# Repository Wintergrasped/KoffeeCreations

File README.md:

# KoffeeCreations

Here you will find all the Open Source files for the KoffeeCreations.cc products P.S Every part of this github and our website is under active development.

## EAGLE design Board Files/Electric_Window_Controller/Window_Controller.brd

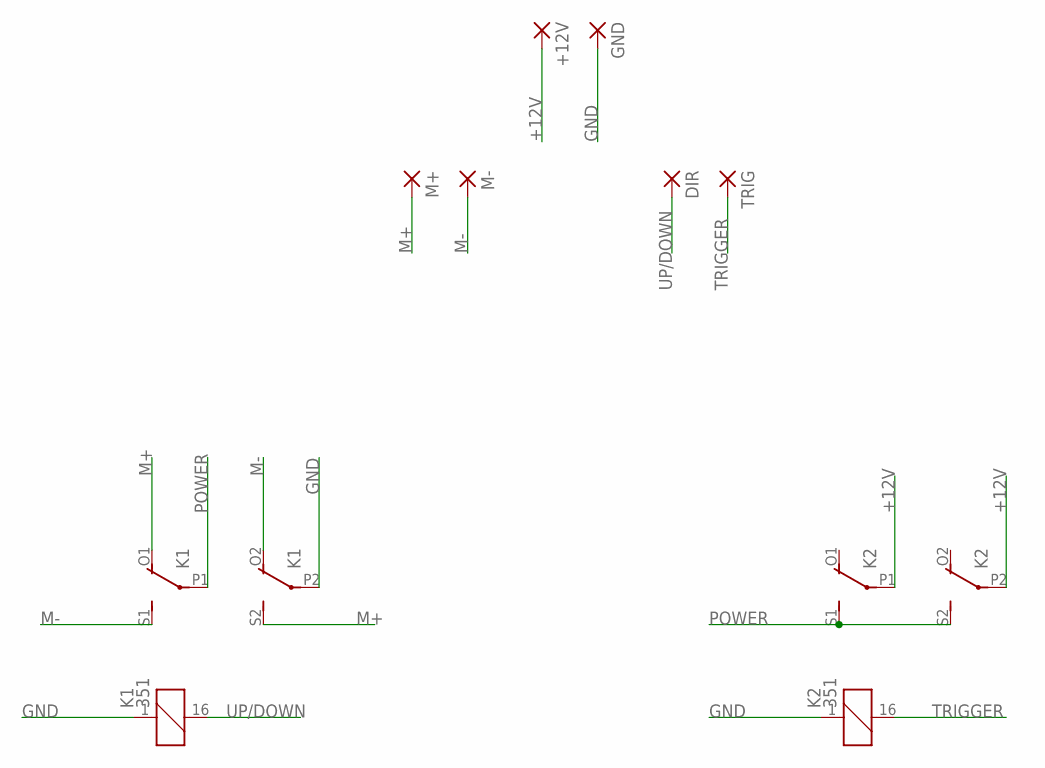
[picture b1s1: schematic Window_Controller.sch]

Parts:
+12V: 3,81/1,4
DIR: 3,81/1,4
GND: 3,81/1,4
K1, K2: 351
M+: 3,81/1,4
M-: 3,81/1,4
TRIG: 3,81/1,4

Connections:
+12V: +12V.1, K2.P1, K2.P2
GND: GND.1, K1.1, K1.P2, K2.1
M+: K1.O1 (O), K1.S2 (S), M+.1
M-: K1.O2 (O), K1.S1 (S), M-.1
POWER: K1.P1, K2.S1 (S), K2.S2 (S)
TRIGGER: K2.16 (2), TRIG.1
UP/DOWN: DIR.1, K1.16 (2)

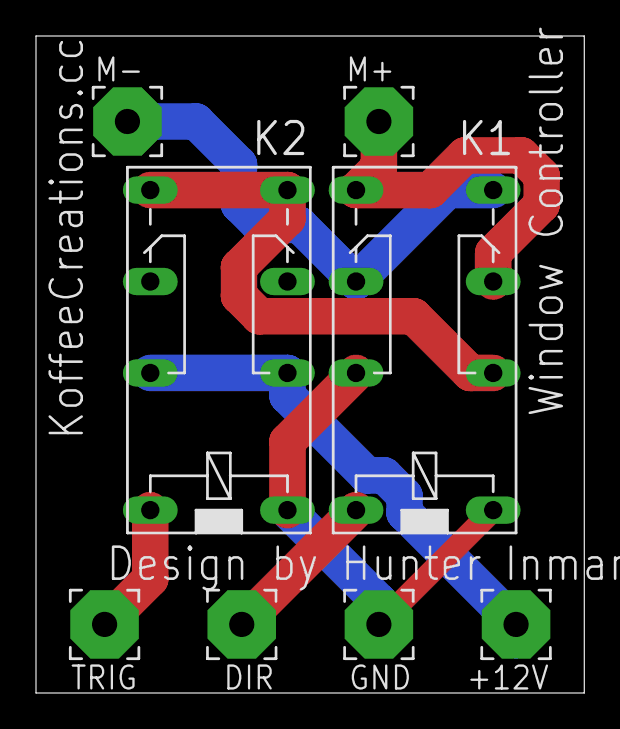
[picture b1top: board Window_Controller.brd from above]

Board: 2 copper layers, 30.5 x 36.5 mm, 8 parts (0 on the bottom side), 7 nets.

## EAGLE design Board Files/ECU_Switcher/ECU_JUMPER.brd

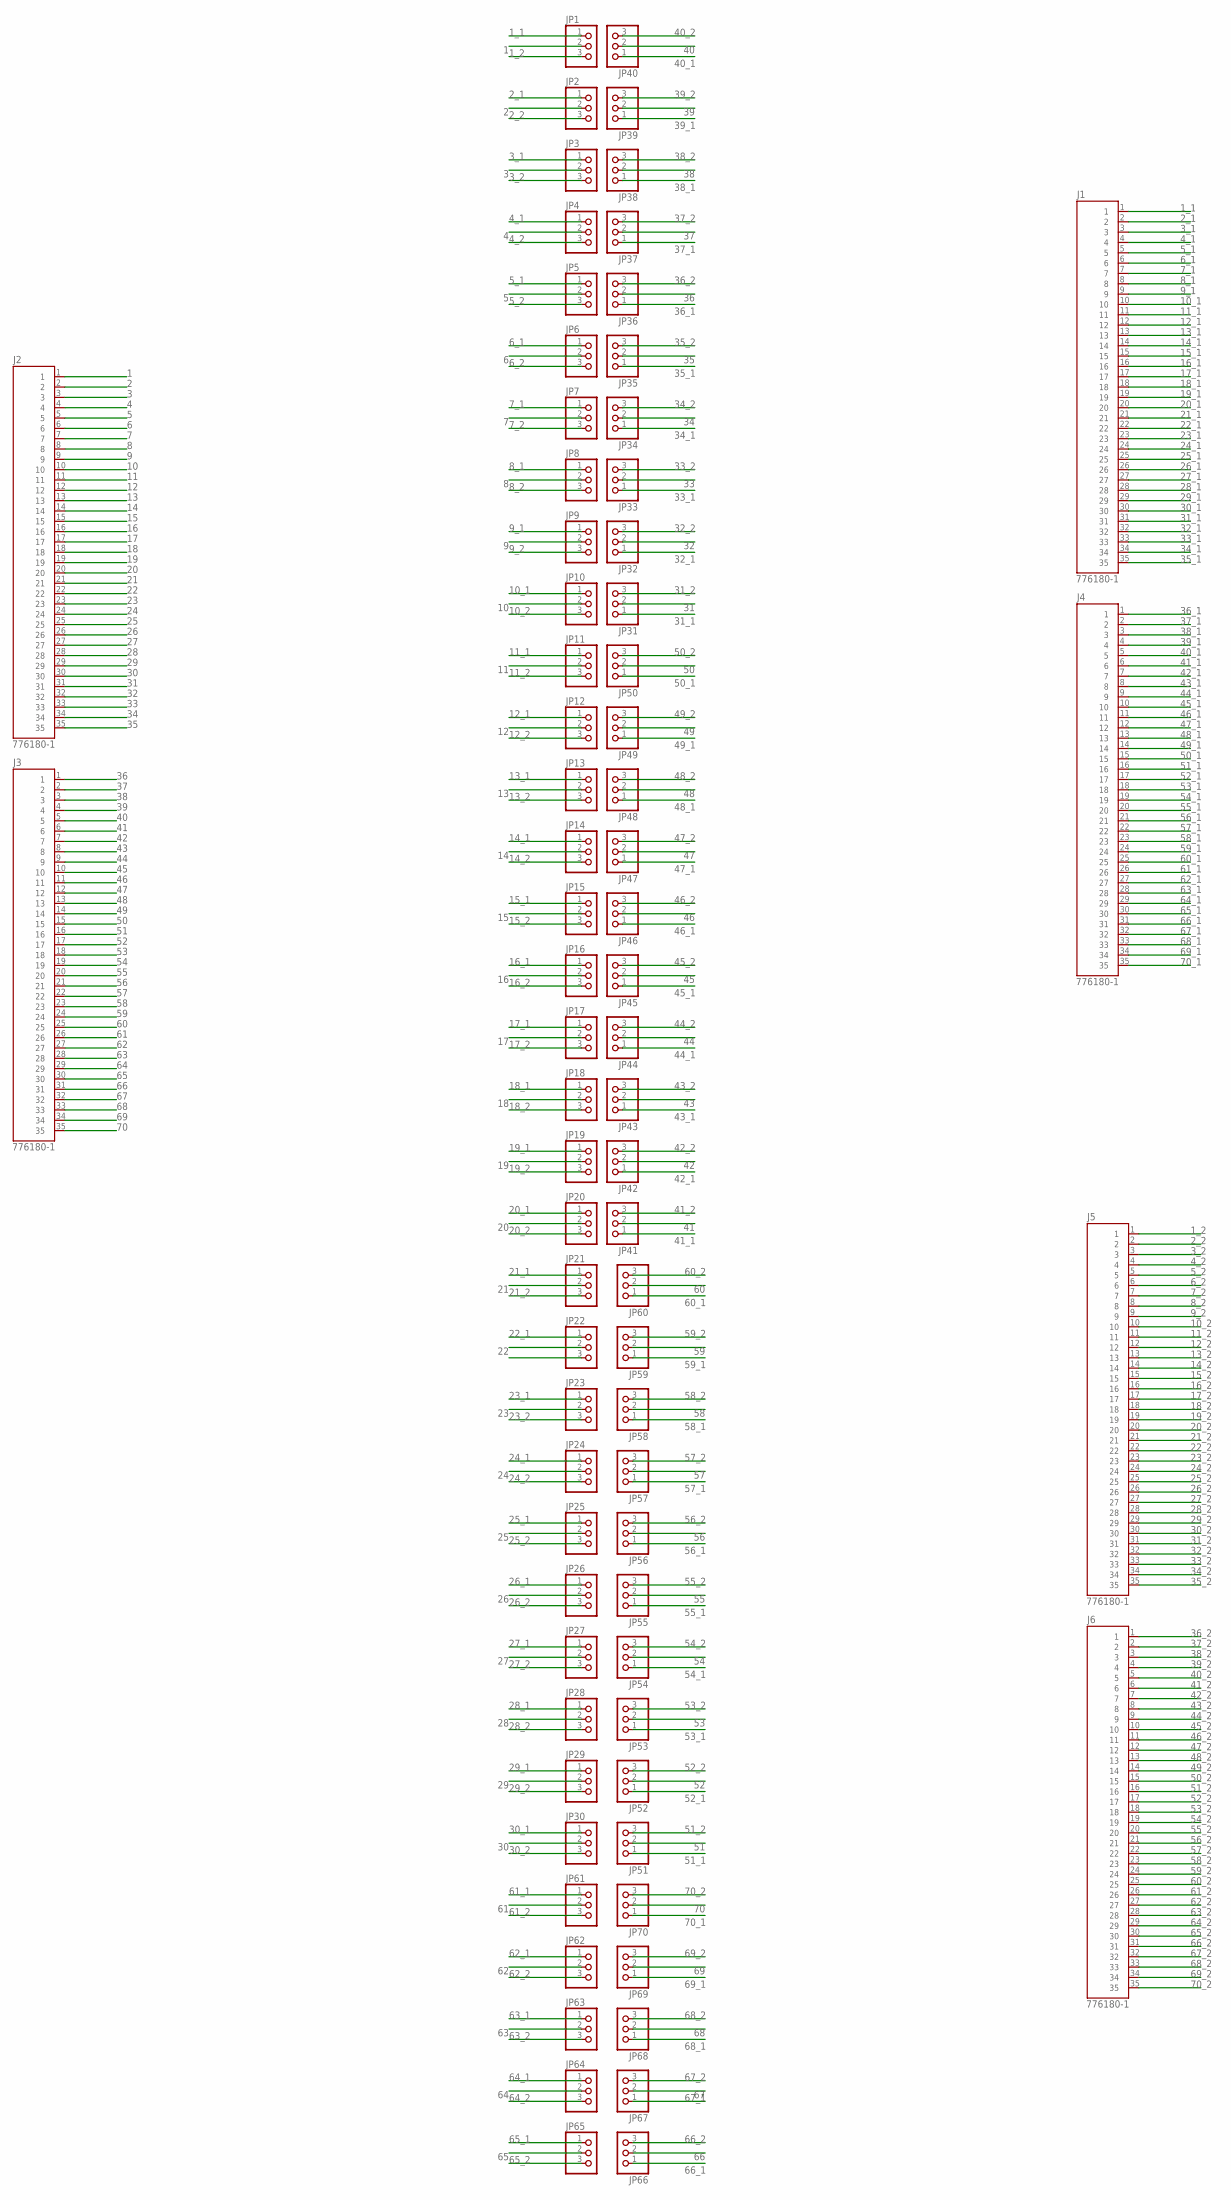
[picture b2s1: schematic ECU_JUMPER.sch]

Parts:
J1, J2, J3, J4, J5, J6: 776180-1; TE_776180-1
JP1, JP2, JP3, JP4, JP5, JP6, JP7, JP8, JP9, JP10, JP11, JP12, JP13, JP14, JP15, JP16, JP17, JP18, JP19, JP20, JP21, JP22, JP23, JP24, JP25, JP26, JP27, JP28, JP29, JP30, JP31, JP32, JP33, JP34, JP35, JP36, JP37, JP38, JP39, JP40, JP41, JP42, JP43, JP44, JP45, JP46, JP47, JP48, JP49, JP50, JP51, JP52, JP53, JP54, JP55, JP56, JP57, JP58, JP59, JP60, JP61, JP62, JP63, JP64, JP65, JP66, JP67, JP68, JP69, JP70: PINHD-1X3; 1X03

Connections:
1: J2.1, JP1.2
1_1: J1.1, JP1.1
1_2: J5.1, JP1.3
2: J2.2, JP2.2
2_1: J1.2, JP2.1
2_2: J5.2, JP2.3
3: J2.3, JP3.2
3_1: J1.3, JP3.1
3_2: J5.3, JP3.3
4: J2.4, JP4.2
4_1: J1.4, JP4.1
4_2: J5.4, JP4.3
5: J2.5, JP5.2
5_1: J1.5, JP5.1
5_2: J5.5, JP5.3
6: J2.6, JP6.2
6_1: J1.6, JP6.1
6_2: J5.6, JP6.3
7: J2.7, JP7.2
7_1: J1.7, JP7.1
7_2: J5.7, JP7.3
8: J2.8, JP8.2
8_1: J1.8, JP8.1
8_2: J5.8, JP8.3
9: J2.9, JP9.2
9_1: J1.9, JP9.1
9_2: J5.9, JP9.3
10: J2.10, JP10.2
10_1: J1.10, JP10.1
10_2: J5.10, JP10.3
11: J2.11, JP11.2
11_1: J1.11, JP11.1
11_2: J5.11, JP11.3
12: J2.12, JP12.2
12_1: J1.12, JP12.1
12_2: J5.12, JP12.3
13: J2.13, JP13.2
13_1: J1.13, JP13.1
13_2: J5.13, JP13.3
14: J2.14, JP14.2
14_1: J1.14, JP14.1
14_2: J5.14, JP14.3
15: J2.15, JP15.2
15_1: J1.15, JP15.1
15_2: J5.15, JP15.3
16: J2.16, JP16.2
16_1: J1.16, JP16.1
16_2: J5.16, JP16.3
17: J2.17, JP17.2
17_1: J1.17, JP17.1
17_2: J5.17, JP17.3
18: J2.18, JP18.2
18_1: J1.18, JP18.1
18_2: J5.18, JP18.3
19: J2.19, JP19.2
19_1: J1.19, JP19.1
19_2: J5.19, JP19.3
20: J2.20, JP20.2
20_1: J1.20, JP20.1
20_2: J5.20, JP20.3
21: J2.21, JP21.2
21_1: J1.21, JP21.1
21_2: J5.21, JP21.3
22: J2.22, JP22.2
22_1: J1.22, JP22.1
22_2: J5.22
23: J2.23, JP23.2
23_1: J1.23, JP23.1
23_2: J5.23, JP23.3
24: J2.24, JP24.2
24_1: J1.24, JP24.1
24_2: J5.24, JP24.3
25: J2.25, JP25.2
25_1: J1.25, JP25.1
25_2: J5.25, JP25.3
26: J2.26, JP26.2
26_1: J1.26, JP26.1
26_2: J5.26, JP26.3
27: J2.27, JP27.2
27_1: J1.27, JP27.1
27_2: J5.27, JP27.3
28: J2.28, JP28.2
28_1: J1.28, JP28.1
28_2: J5.28, JP28.3
29: J2.29, JP29.2
29_1: J1.29, JP29.1
29_2: J5.29, JP29.3
30: J2.30, JP30.2
30_1: J1.30, JP30.1
30_2: J5.30, JP30.3
31: J2.31, JP31.2
31_1: J1.31, JP31.1
31_2: J5.31, JP31.3
32: J2.32, JP32.2
32_1: J1.32, JP32.1
32_2: J5.32, JP32.3
33: J2.33, JP33.2
33_1: J1.33, JP33.1
33_2: J5.33, JP33.3
34: J2.34, JP34.2
34_1: J1.34, JP34.1
34_2: J5.34, JP34.3
35: J2.35, JP35.2
35_1: J1.35, JP35.1
35_2: J5.35, JP35.3
36: J3.1, JP36.2
36_1: J4.1, JP36.1
36_2: J6.1, JP36.3
37: J3.2, JP37.2
37_1: J4.2, JP37.1
37_2: J6.2, JP37.3
38: J3.3, JP38.2
38_1: J4.3, JP38.1
38_2: J6.3, JP38.3
39: J3.4, JP39.2
39_1: J4.4, JP39.1
39_2: J6.4, JP39.3
40: J3.5, JP40.2
40_1: J4.5, JP40.1
40_2: J6.5, JP40.3
41: J3.6, JP41.2
41_1: J4.6, JP41.1
41_2: J6.6, JP41.3
42: J3.7, JP42.2
42_1: J4.7, JP42.1
42_2: J6.7, JP42.3
43: J3.8, JP43.2
43_1: J4.8, JP43.1
43_2: J6.8, JP43.3
44: J3.9, JP44.2
44_1: J4.9, JP44.1
44_2: J6.9, JP44.3
45: J3.10, JP45.2
45_1: J4.10, JP45.1
45_2: J6.10, JP45.3
46: J3.11, JP46.2
46_1: J4.11, JP46.1
46_2: J6.11, JP46.3
47: J3.12, JP47.2
47_1: J4.12, JP47.1
47_2: J6.12, JP47.3
48: J3.13, JP48.2
48_1: J4.13, JP48.1
48_2: J6.13, JP48.3
49: J3.14, JP49.2
49_1: J4.14, JP49.1
49_2: J6.14, JP49.3
50: J3.15, JP50.2
50_1: J4.15, JP50.1
50_2: J6.15, JP50.3
51: J3.16, JP51.2
51_1: J4.16, JP51.1
51_2: J6.16, JP51.3
52: J3.17, JP52.2
52_1: J4.17, JP52.1
52_2: J6.17, JP52.3
53: J3.18, JP53.2
53_1: J4.18, JP53.1
53_2: J6.18, JP53.3
54: J3.19, JP54.2
54_1: J4.19, JP54.1
54_2: J6.19, JP54.3
55: J3.20, JP55.2
55_1: J4.20, JP55.1
55_2: J6.20, JP55.3
56: J3.21, JP56.2
56_1: J4.21, JP56.1
56_2: J6.21, JP56.3
57: J3.22, JP57.2
57_1: J4.22, JP57.1
57_2: J6.22, JP57.3
58: J3.23, JP58.2
58_1: J4.23, JP58.1
58_2: J6.23, JP58.3
59: J3.24, JP59.2
59_1: J4.24, JP59.1
59_2: J6.24, JP59.3
60: J3.25, JP60.2
60_1: J4.25, JP60.1
60_2: J6.25, JP60.3
61: J3.26, JP61.2
61_1: J4.26, JP61.1
61_2: J6.26, JP61.3
62: J3.27, JP62.2
62_1: J4.27, JP62.1
62_2: J6.27, JP62.3
63: J3.28, JP63.2
63_1: J4.28, JP63.1
63_2: J6.28, JP63.3
64: J3.29, JP64.2
64_1: J4.29, JP64.1
64_2: J6.29, JP64.3
65: J3.30, JP65.2
65_1: J4.30, JP65.1
65_2: J6.30, JP65.3
66: J3.31, JP66.2
66_1: J4.31, JP66.1
66_2: J6.31, JP66.3
67: J3.32, JP67.2
67_1: J4.32, JP67.1
67_2: J6.32, JP67.3
68: J3.33, JP68.2
68_1: J4.33, JP68.1
68_2: J6.33, JP68.3
69: J3.34, JP69.2
69_1: J4.34, JP69.1
69_2: J6.34, JP69.3
70: J3.35, JP70.2
70_1: J4.35, JP70.1
70_2: J6.35, JP70.3

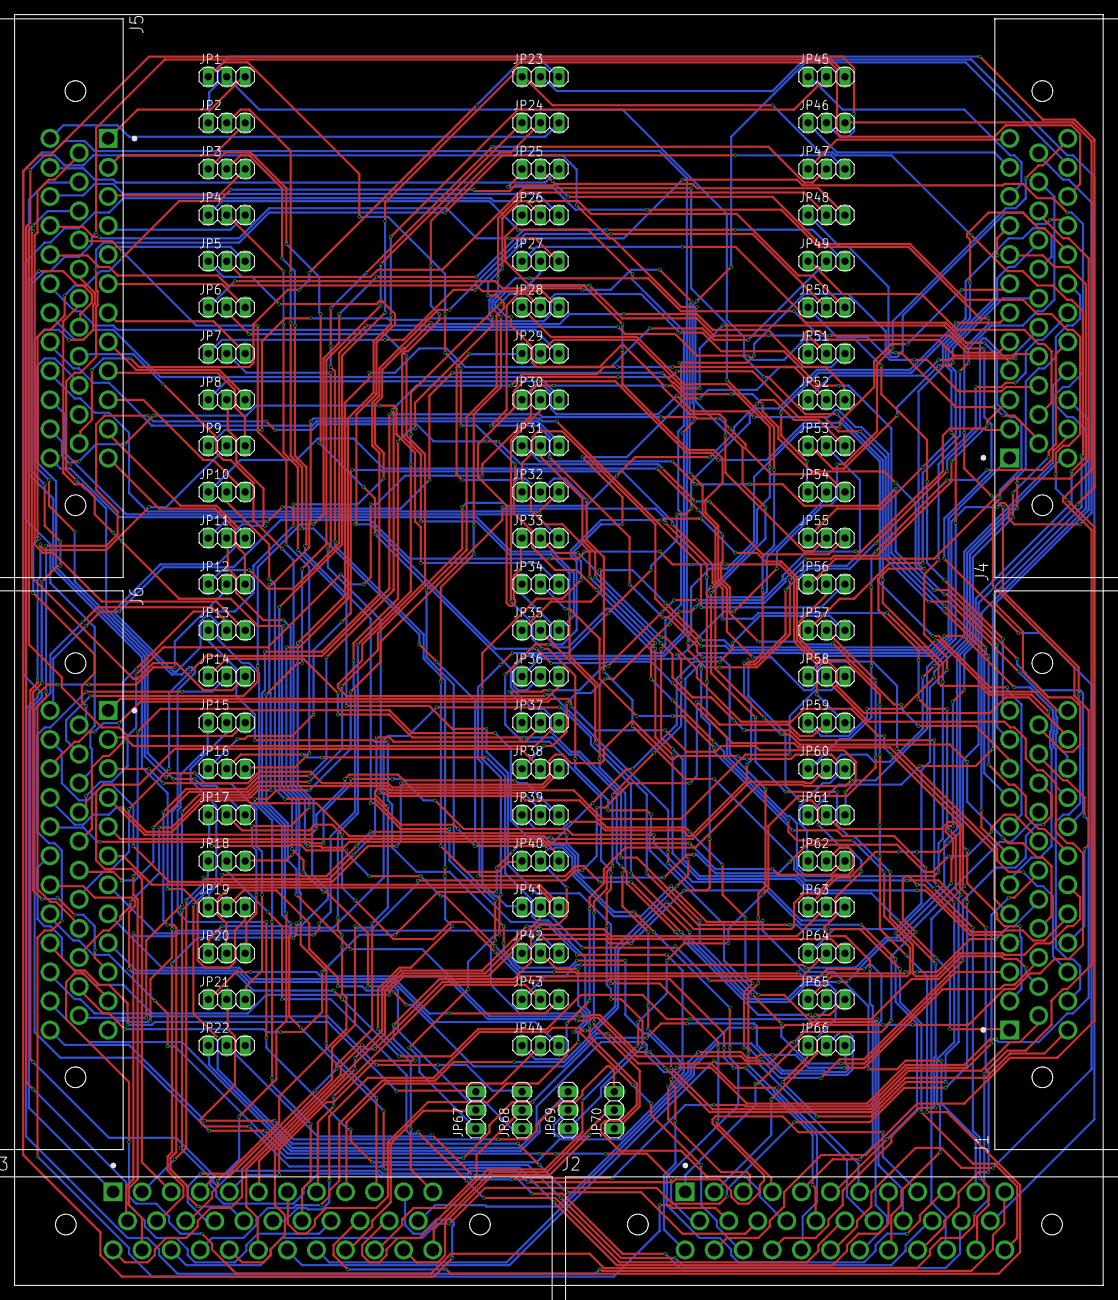
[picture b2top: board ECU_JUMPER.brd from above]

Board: 2 copper layers, 149.8 x 174.9 mm, 76 parts (0 on the bottom side), 209 nets.

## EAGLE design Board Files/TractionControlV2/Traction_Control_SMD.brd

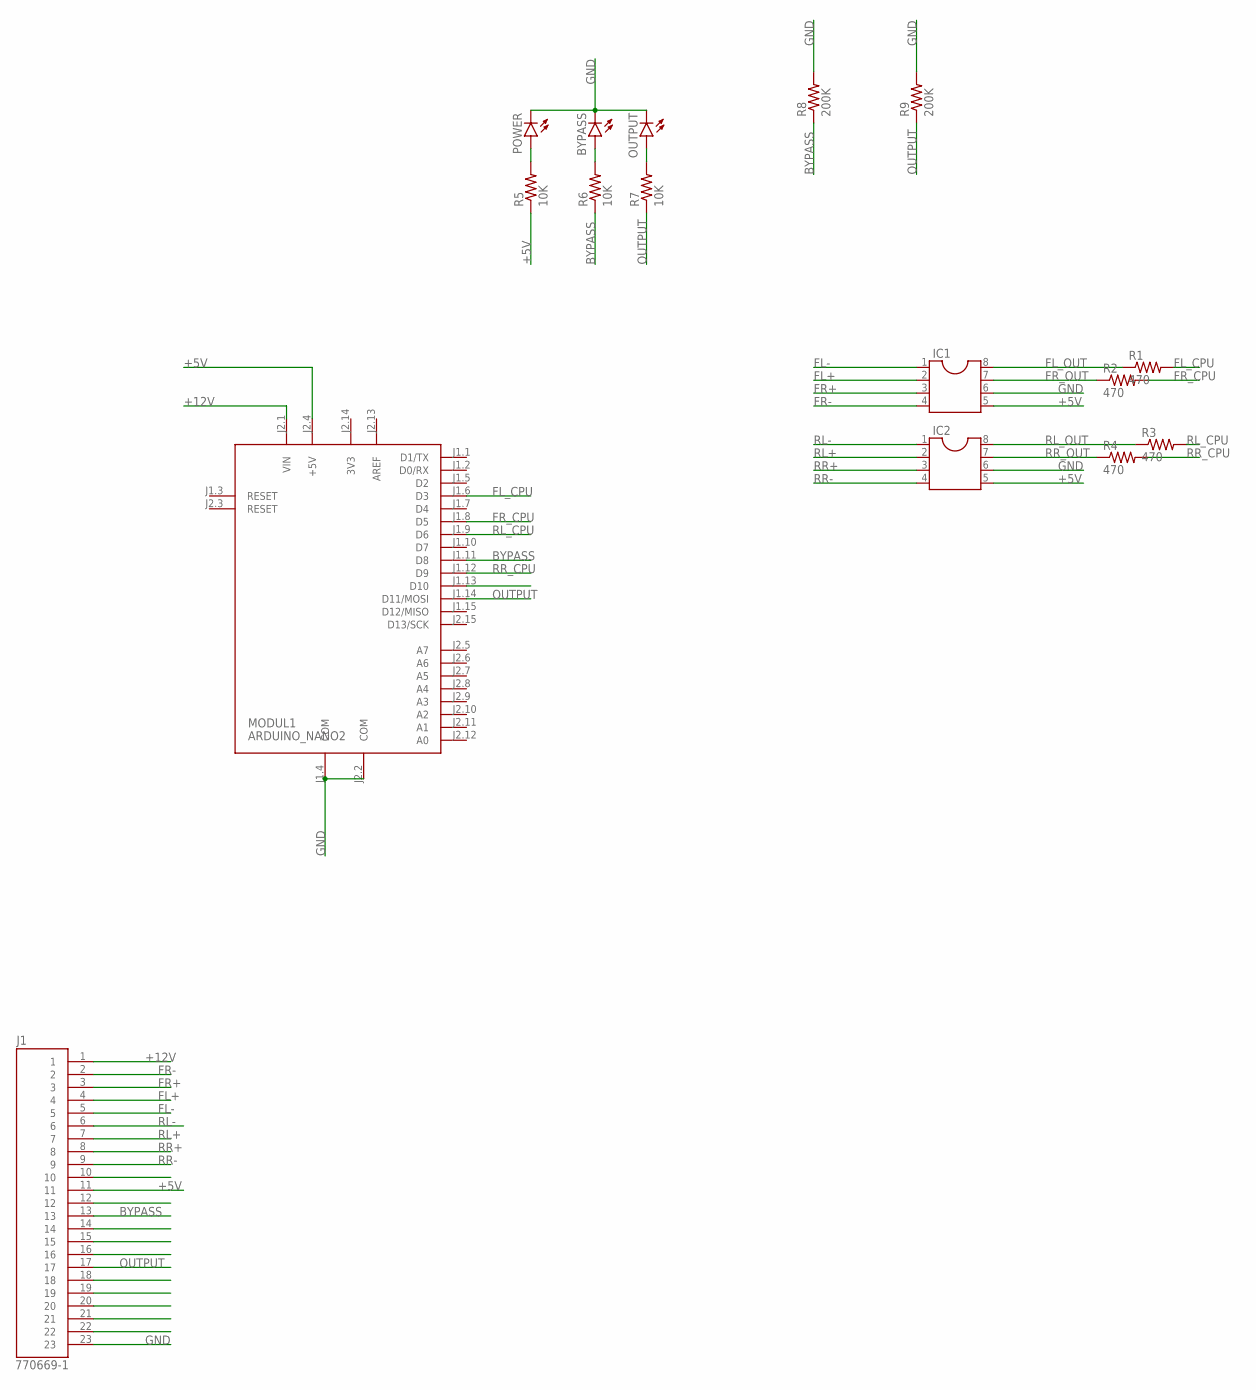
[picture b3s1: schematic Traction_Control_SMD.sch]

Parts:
BYPASS: LEDCHIP-LED0805; CHIP-LED0805
IC1, IC2: DIL8S; SOCKET-08
J1: 770669-1; TE_770669-1
MODUL1: ARDUINO_NANO2
OUTPUT: LEDCHIP-LED0805; CHIP-LED0805
POWER: LEDCHIP-LED0805; CHIP-LED0805
R1, R2, R3, R4: 470; R0805
R5, R6, R7: 10K; R0805
R8, R9: 200K; R0805

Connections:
3V3: MODUL1.J2.14 (3V3)
+5V: IC1.5, IC2.5, J1.11, MODUL1.J2.4 (+5V), R5.1
+12V: J1.1, MODUL1.J2.1 (VIN)
AREF: MODUL1.J2.13 (AREF)
BYPASS: J1.13, MODUL1.J1.11 (D8), R6.1, R8.1
FL+: IC1.2, J1.4
FL-: IC1.1, J1.5
FL_CPU: MODUL1.J1.6 (D3), R1.2
FL_OUT: IC1.8, R1.1
FR+: IC1.3, J1.3
FR-: IC1.4, J1.2
FR_CPU: MODUL1.J1.8 (D5), R2.2
FR_OUT: IC1.7, R2.1
GND: BYPASS.C, IC1.6, IC2.6, J1.23, MODUL1.J1.4 (COM), MODUL1.J2.2 (COM), OUTPUT.C, POWER.C, R8.2, R9.2
unnamed: POWER.A, R5.2
unnamed: BYPASS.A, R6.2
unnamed: OUTPUT.A, R7.2
OUTPUT: J1.17, MODUL1.J1.14 (D11/MOSI), R7.1, R9.1
RL+: IC2.2, J1.7
RL-: IC2.1, J1.6
RL_CPU: MODUL1.J1.9 (D6), R3.2
RL_OUT: IC2.8, R3.1
RR+: IC2.3, J1.8
RR-: IC2.4, J1.9
RR_CPU: MODUL1.J1.12 (D9), R4.2
RR_OUT: IC2.7, R4.1

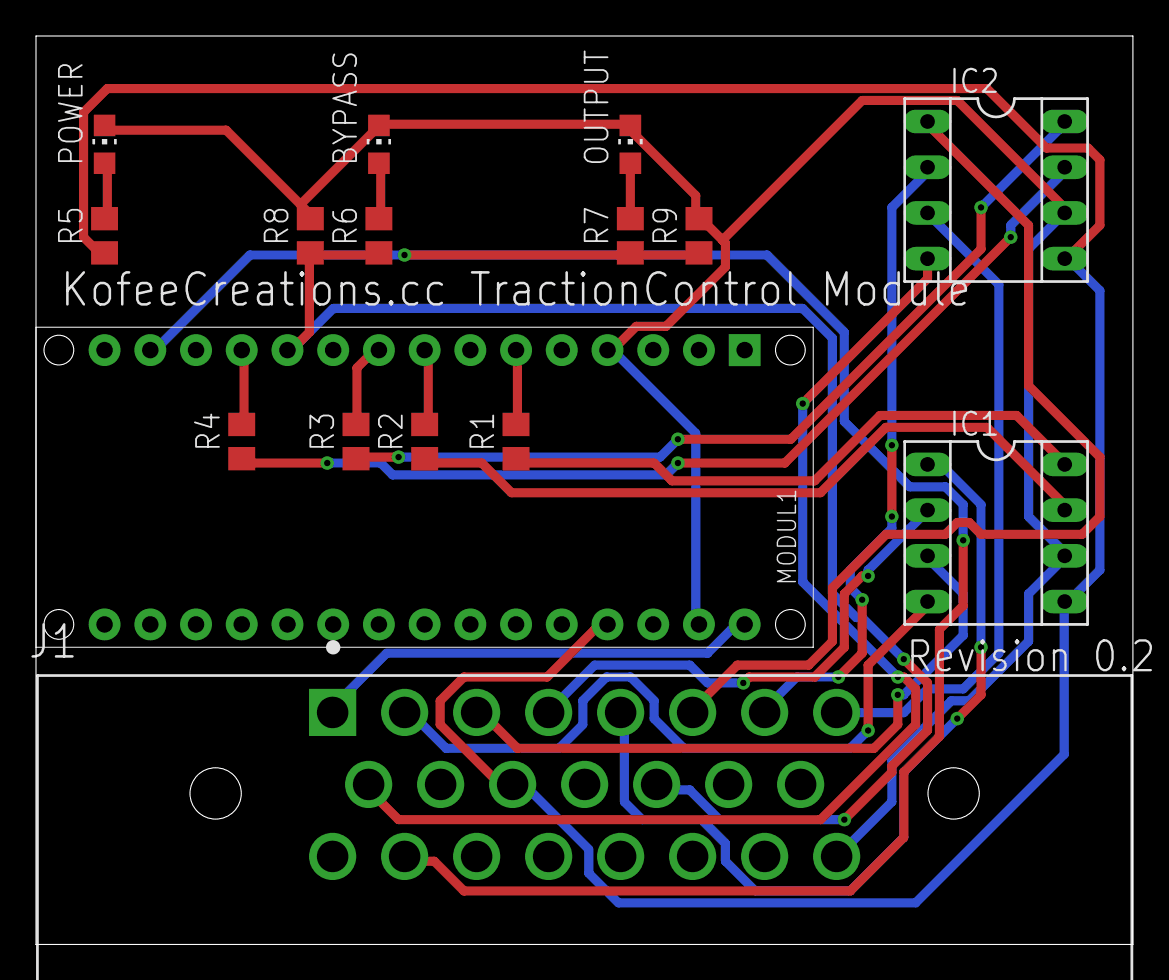
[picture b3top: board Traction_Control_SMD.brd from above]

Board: 2 copper layers, 60.9 x 50.5 mm, 16 parts (0 on the bottom side), 24 nets.

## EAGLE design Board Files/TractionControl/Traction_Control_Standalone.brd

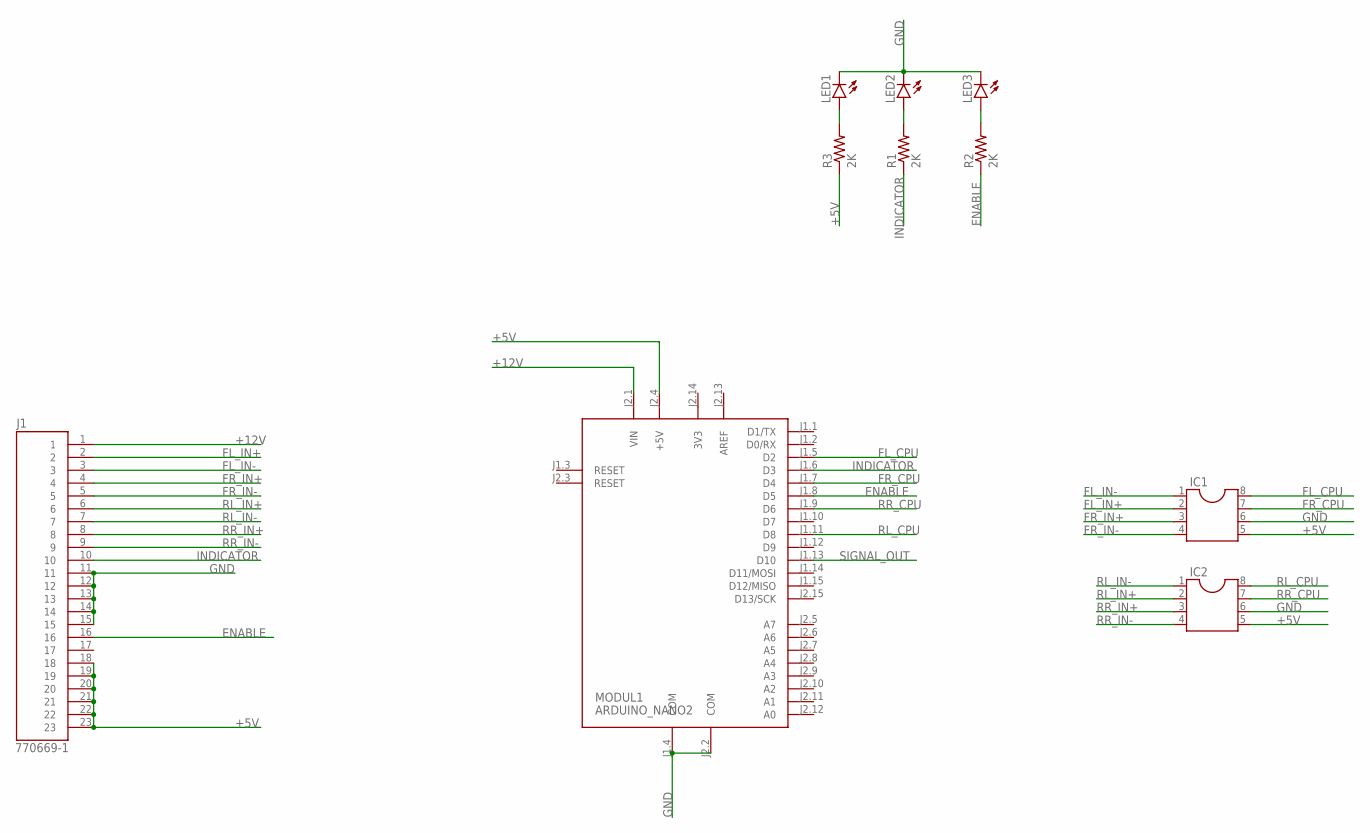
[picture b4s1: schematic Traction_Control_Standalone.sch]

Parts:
IC1, IC2: DIL8S; SOCKET-08
J1: 770669-1; TE_770669-1
LED1, LED2, LED3: LEDCHIP-LED0805; CHIP-LED0805
MODUL1: ARDUINO_NANO2
R1, R2, R3: 2K; R0805

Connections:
3V3: MODUL1.J2.14 (3V3)
+5V: IC1.5, IC2.5, J1.18, J1.19, J1.20, J1.21, J1.22, J1.23, MODUL1.J2.4 (+5V), R3.1
+12V: J1.1, MODUL1.J2.1 (VIN)
AREF: MODUL1.J2.13 (AREF)
ENABLE: J1.16, MODUL1.J1.8 (D5), R2.1
FL_CPU: IC1.8, MODUL1.J1.5 (D2)
FL_IN+: IC1.2, J1.2
FL_IN-: IC1.1, J1.3
FR_CPU: IC1.7, MODUL1.J1.7 (D4)
FR_IN+: IC1.3, J1.4
FR_IN-: IC1.4, J1.5
GND: IC1.6, IC2.6, J1.11, J1.12, J1.13, J1.14, J1.15, LED1.C, LED2.C, LED3.C, MODUL1.J1.4 (COM), MODUL1.J2.2 (COM)
INDICATOR: J1.10, MODUL1.J1.6 (D3), R1.1
unnamed: LED1.A, R3.2
unnamed: LED2.A, R1.2
unnamed: LED3.A, R2.2
RL_CPU: IC2.8, MODUL1.J1.11 (D8)
RL_IN+: IC2.2, J1.6
RL_IN-: IC2.1, J1.7
RR_CPU: IC2.7, MODUL1.J1.9 (D6)
RR_IN+: IC2.3, J1.8
RR_IN-: IC2.4, J1.9
SIGNAL_OUT: MODUL1.J1.13 (D10)

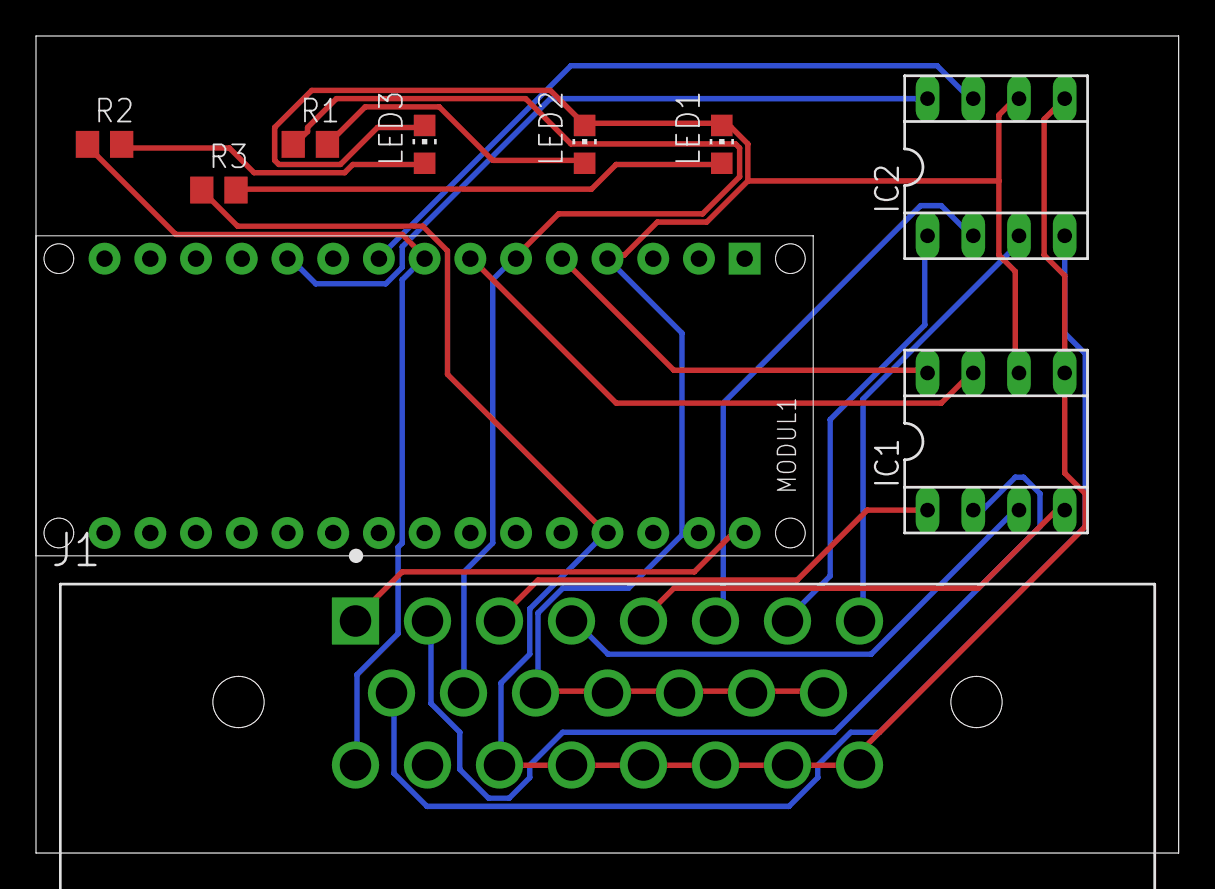
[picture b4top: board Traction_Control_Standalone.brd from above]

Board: 2 copper layers, 63.5 x 45.4 mm, 10 parts (0 on the bottom side), 20 nets.

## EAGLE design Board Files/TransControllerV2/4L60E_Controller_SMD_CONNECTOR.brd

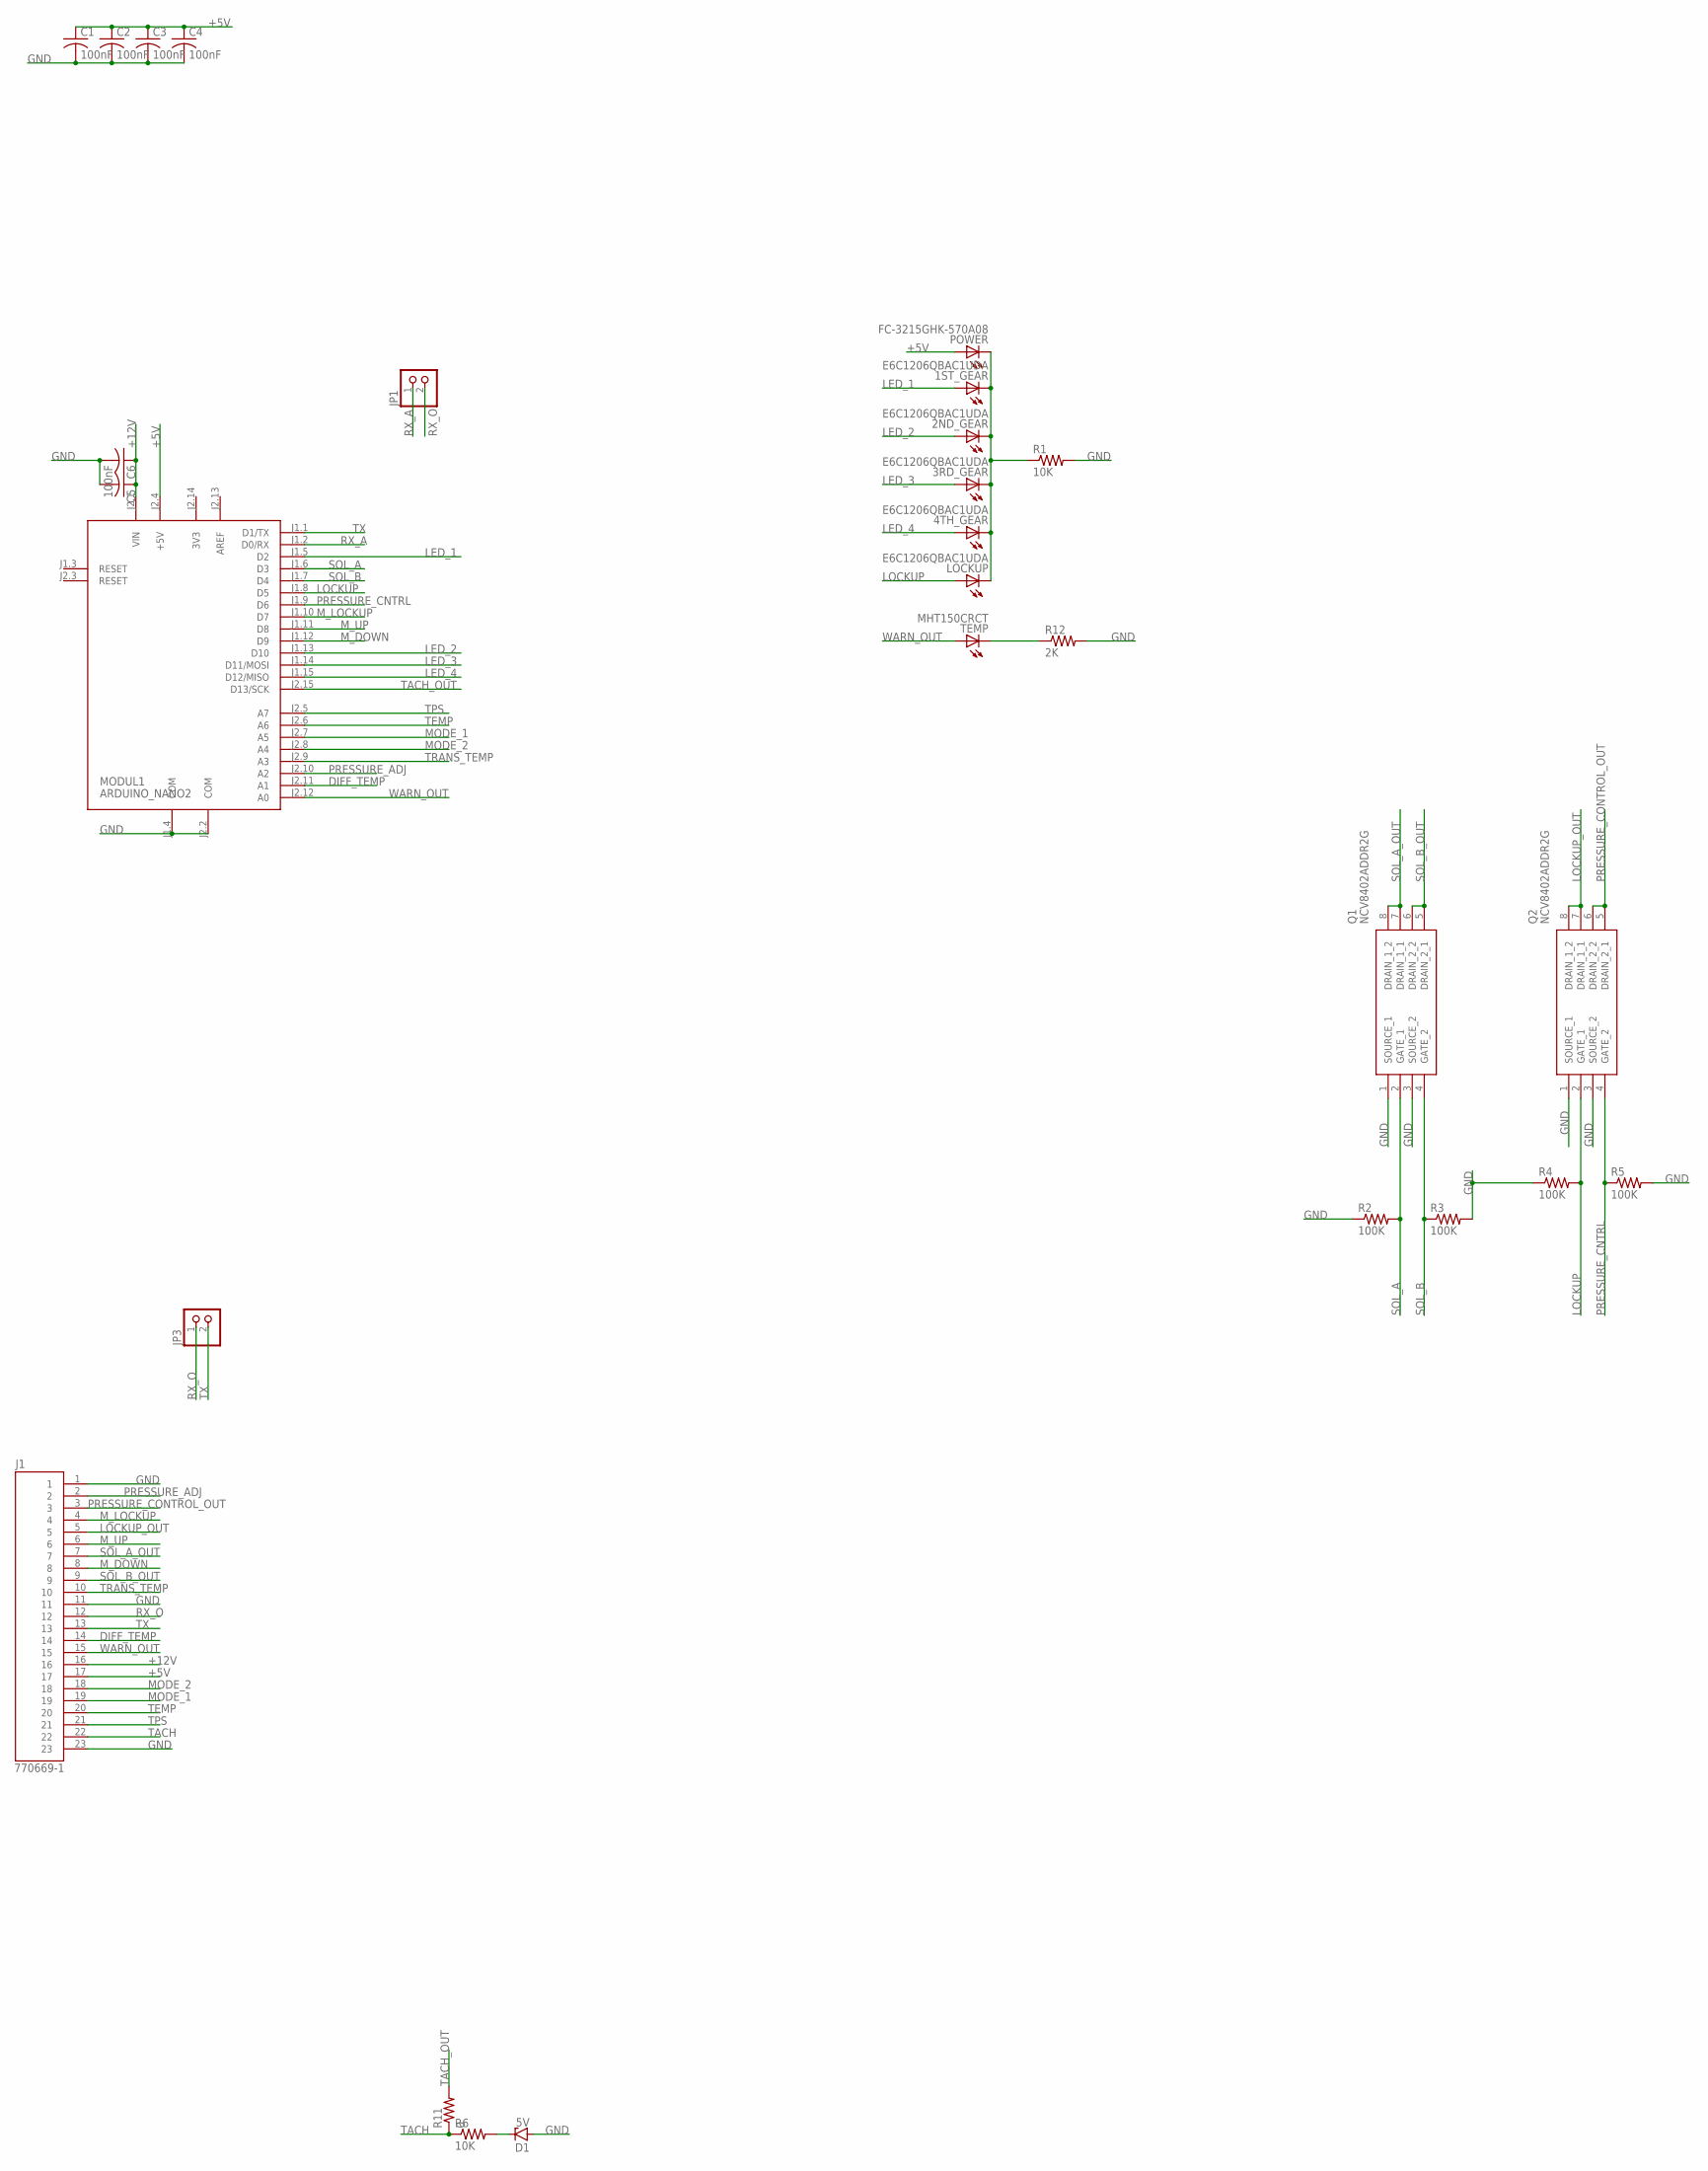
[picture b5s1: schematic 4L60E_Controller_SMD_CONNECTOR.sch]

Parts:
1ST_GEAR, 2ND_GEAR, 3RD_GEAR, 4TH_GEAR: E6C1206QBAC1UDA; LED_1206
C1, C2, C3, C4: 100nF; C0805
C5: C-USC1206; C1206
C6: 100nF; C1206
D1: 5V; SOT23
J1: 770669-1; TE_770669-1
JP1, JP3: PINHD-1X2; 1X02
LOCKUP: E6C1206QBAC1UDA; LED_1206
MODUL1: ARDUINO_NANO2
POWER: FC-3215GHK-570A08; LED_1206
Q1, Q2: NCV8402ADDR2G; SOIC127P600X175-8N
R1: 10K; M0805
R2, R3, R4, R5: 100K; R0805
R6: 10K; R0805
R11: 0; R0805
R12: 2K; R0805
TEMP: MHT150CRCT; LED_1206

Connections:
3V3: MODUL1.J2.14 (3V3)
+5V: C1.1, C2.1, C3.1, C4.1, J1.17, MODUL1.J2.4 (+5V), POWER.A
+12V: C5.1, C6.1, J1.16, MODUL1.J2.1 (VIN)
AREF: MODUL1.J2.13 (AREF)
DIFF_TEMP: J1.14, MODUL1.J2.11 (A1)
GND: C1.2, C2.2, C3.2, C4.2, C5.2, C6.2, D1.1 (A), J1.1, J1.11, J1.23, MODUL1.J1.4 (COM), MODUL1.J2.2 (COM), Q1.1 (SOURCE_1), Q1.3 (SOURCE_2), Q2.1 (SOURCE_1), Q2.3 (SOURCE_2), R1.2, R2.1, R3.2, R4.1, R5.2, R12.2
LED_1: 1ST_GEAR.A, MODUL1.J1.5 (D2)
LED_2: 2ND_GEAR.A, MODUL1.J1.13 (D10)
LED_3: 3RD_GEAR.A, MODUL1.J1.14 (D11/MOSI)
LED_4: 4TH_GEAR.A, MODUL1.J1.15 (D12/MISO)
LOCKUP: LOCKUP.A, MODUL1.J1.8 (D5), Q2.2 (GATE_1), R4.2
LOCKUP_OUT: J1.5, Q2.7 (DRAIN_1_1), Q2.8 (DRAIN_1_2)
MODE_1: J1.19, MODUL1.J2.7 (A5)
MODE_2: J1.18, MODUL1.J2.8 (A4)
M_DOWN: J1.8, MODUL1.J1.12 (D9)
M_LOCKUP: J1.4, MODUL1.J1.10 (D7)
M_UP: J1.6, MODUL1.J1.11 (D8)
unnamed: D1.3 (C), R6.2
unnamed: R12.1, TEMP.C
unnamed: 1ST_GEAR.C, 2ND_GEAR.C, 3RD_GEAR.C, 4TH_GEAR.C, LOCKUP.C, POWER.C, R1.1
PRESSURE_ADJ: J1.2, MODUL1.J2.10 (A2)
PRESSURE_CNTRL: MODUL1.J1.9 (D6), Q2.4 (GATE_2), R5.1
PRESSURE_CONTROL_OUT: J1.3, Q2.5 (DRAIN_2_1), Q2.6 (DRAIN_2_2)
RX_A: JP1.1, MODUL1.J1.2 (D0/RX)
RX_O: J1.12, JP1.2, JP3.1
SOL_A: MODUL1.J1.6 (D3), Q1.2 (GATE_1), R2.2
SOL_A_OUT: J1.7, Q1.7 (DRAIN_1_1), Q1.8 (DRAIN_1_2)
SOL_B: MODUL1.J1.7 (D4), Q1.4 (GATE_2), R3.1
SOL_B_OUT: J1.9, Q1.5 (DRAIN_2_1), Q1.6 (DRAIN_2_2)
TACH: J1.22, R6.1, R11.1
TACH_OUT: MODUL1.J2.15 (D13/SCK), R11.2
TEMP: J1.20, MODUL1.J2.6 (A6)
TPS: J1.21, MODUL1.J2.5 (A7)
TRANS_TEMP: J1.10, MODUL1.J2.9 (A3)
TX: J1.13, JP3.2, MODUL1.J1.1 (D1/TX)
WARN_OUT: J1.15, MODUL1.J2.12 (A0), TEMP.A

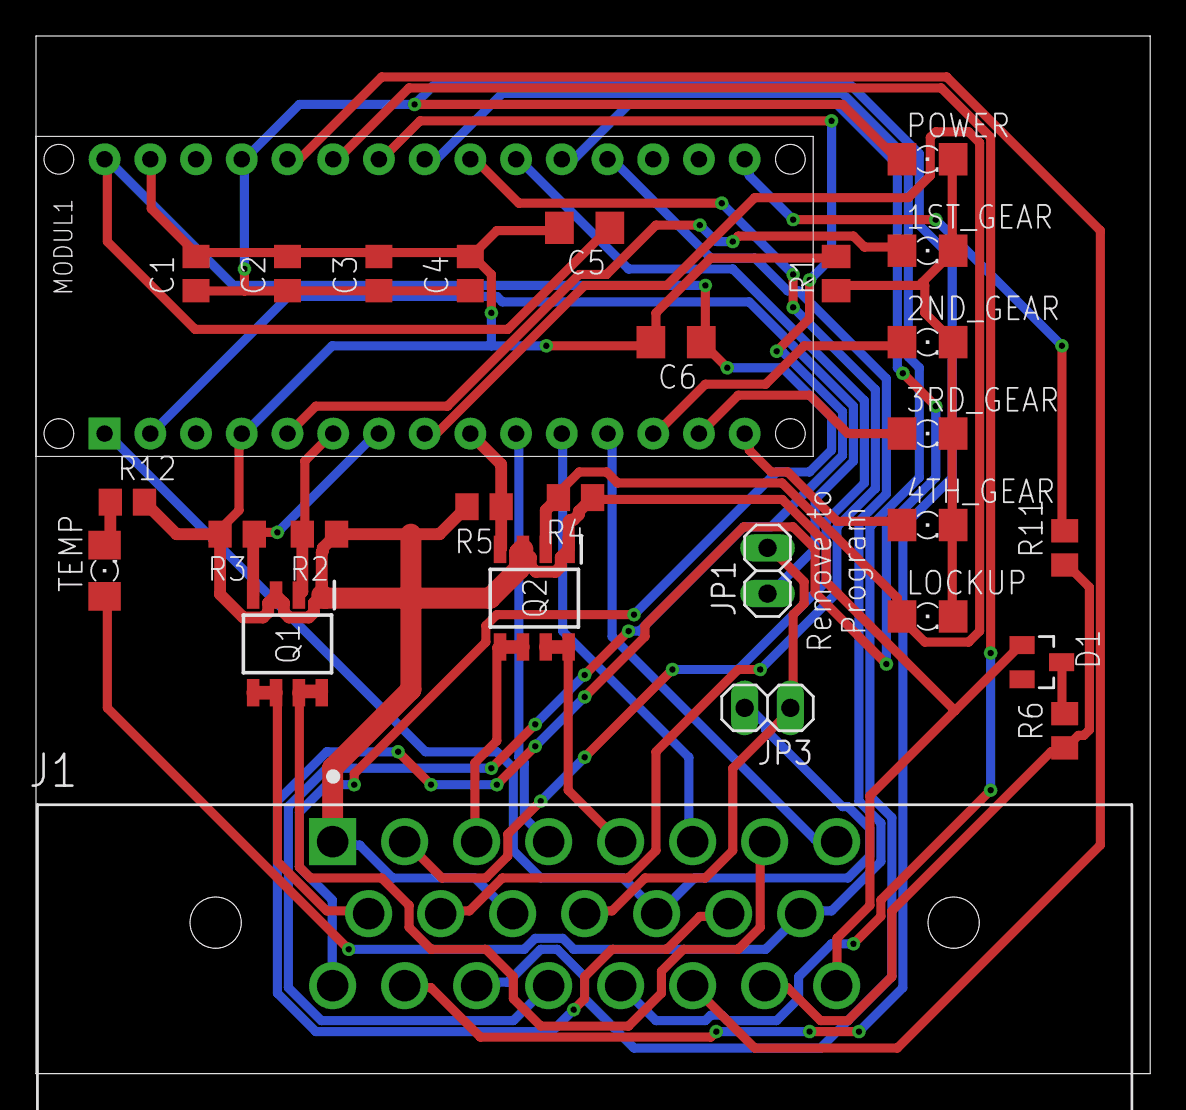
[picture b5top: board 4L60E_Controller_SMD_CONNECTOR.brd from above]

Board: 2 copper layers, 61.9 x 57.6 mm, 28 parts (0 on the bottom side), 34 nets.
